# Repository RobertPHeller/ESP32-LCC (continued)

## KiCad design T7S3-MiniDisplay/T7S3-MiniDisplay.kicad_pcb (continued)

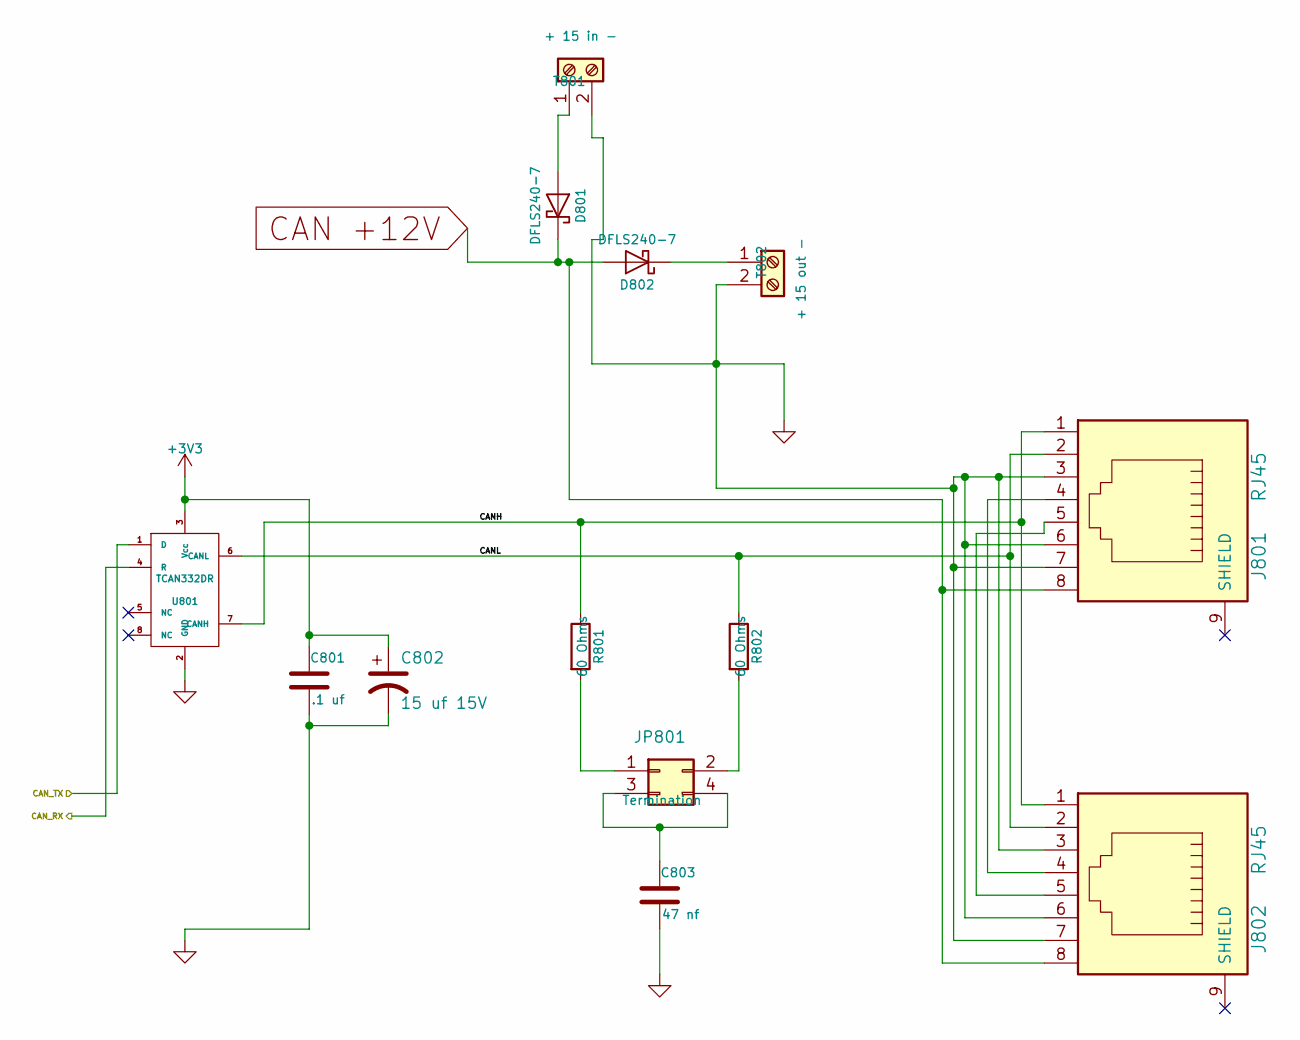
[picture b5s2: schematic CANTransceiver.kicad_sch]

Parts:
C801: .1 uf; C_0603_1608Metric; Mouser Part Number 80-C0603C104K5R7411
C802: 15 uf 15V; CP_Elec_4x5.7; Mouser Part Number 710-865080340002
C803: 47 nf; C_0603_1608Metric; Mouser Part Number 710-885012206093
D801, D802: DFLS240-7; D_PowerDI-123; Mouser Part Number 621-DFLS240-7
J801, J802: RJ45; RJ45_8N-S; Mouser Part Number 710-615008144221
JP801: Termination; PinHeader_2x02_P2.54mm_Vertical; Mouser Part Number 649-67997-404HLF
R801, R802: 60 Ohms; R_1206_3216Metric; Mouser Part Number 71-CRCW120660R0KNAIF
T801: + 15 in -; TerminalBlock_TE_282834-2_1x02_P2.54mm_Horizontal; Mouser Part Number 651-1725656
T802: + 15 out -; TerminalBlock_TE_282834-2_1x02_P2.54mm_Horizontal; Mouser Part Number 651-1725656
U801: TCAN332DR; SOIC-8_3.9x4.9mm_P1.27mm; Mouser Part Number 595-TCAN332DR

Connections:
+3V3: C801.1, C802.1, U801.3 (Vcc); also elsewhere on the board
/CAN Rx: U801.4 (R); also elsewhere on the board
/CAN Transceiver/CANH: J801.1, J802.1, R801.1, U801.7 (CANH)
/CAN Transceiver/CANL: J801.2, J802.2, R802.1, U801.6 (CANL)
/CAN Tx: U801.1 (D); also elsewhere on the board
CAN +12V: D801.1 (K), D802.2 (A), J801.8, J802.8; also elsewhere on the board
GND: C801.2, C802.2, C803.2, J801.3, J801.6, J801.7, J802.3, J802.6, J802.7, T801.2, T802.2, U801.2 (GND); also elsewhere on the board
unnamed: C803.1, JP801.3, JP801.4
unnamed: D801.2 (A), T801.1
unnamed: D802.1 (K), T802.1
unnamed: J801.4, J802.4
unnamed: J801.5, J802.5
unnamed: JP801.1, R801.2
unnamed: JP801.2, R802.2

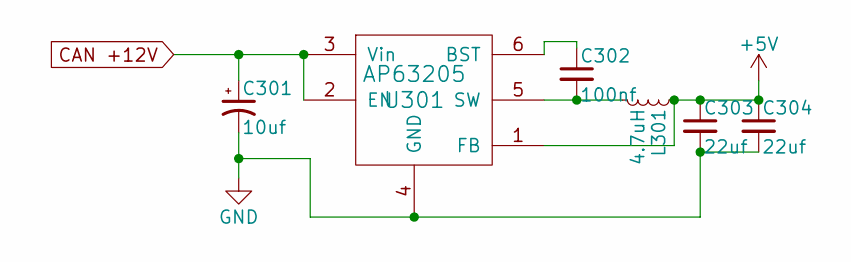
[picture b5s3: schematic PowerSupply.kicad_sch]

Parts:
C301: 10uf; CP_Elec_5x5.3; Mouser Part Number 667-EEE-HB1C100R
C302: 100nf; C_0603_1608Metric; Mouser Part Number 710-885012206020
C303, C304: 22uf; C_0603_1608Metric; Mouser Part Number 603-CC0603MRX6S5B226
L301: 4.7uH; L_7.3x7.3_H4.5; Mouser Part Number 81-B1047AS-4R7N=P3
U301: AP63205; TSOT-23-6; Mouser Part Number 621-AP63205WU-7

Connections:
+5V: C303.1, C304.1, L301.1, U301.1 (FB); also elsewhere on the board
CAN +12V: C301.1, U301.2 (EN), U301.3 (Vin); also elsewhere on the board
GND: C301.2, C303.2, C304.2, U301.4 (GND); also elsewhere on the board
unnamed: C302.1, U301.6 (BST)
unnamed: C302.2, L301.2, U301.5 (SW)

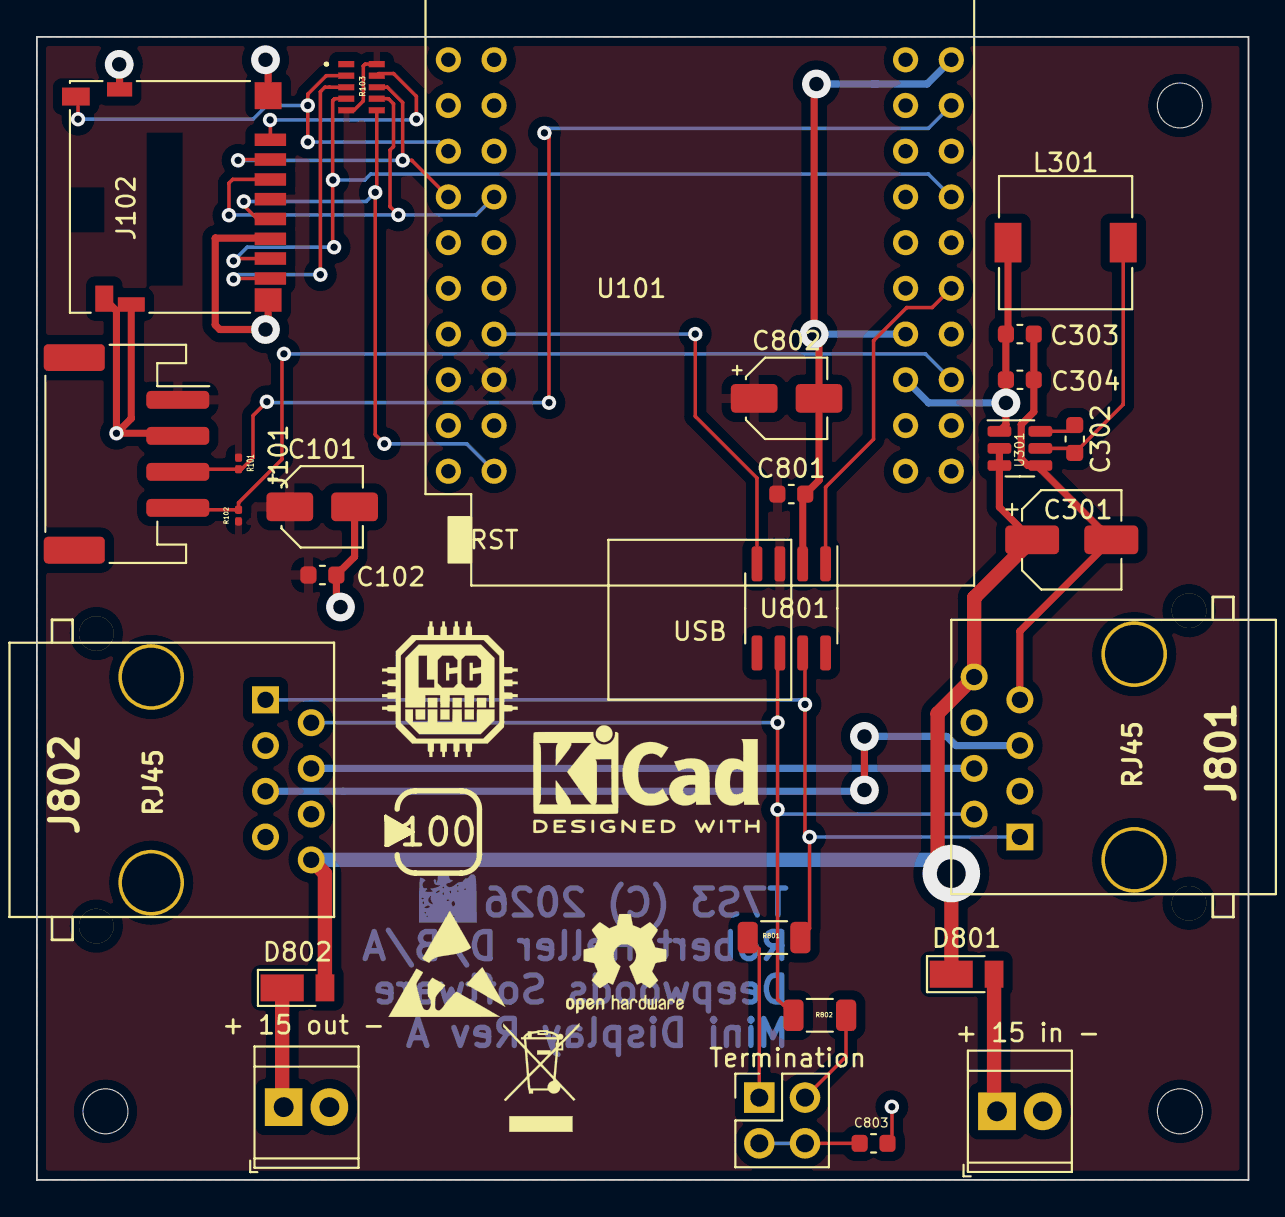
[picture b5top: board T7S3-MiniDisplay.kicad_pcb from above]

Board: 2 copper layers, 67.3 x 63.5 mm, 30 parts (0 on the bottom side), 26 nets.

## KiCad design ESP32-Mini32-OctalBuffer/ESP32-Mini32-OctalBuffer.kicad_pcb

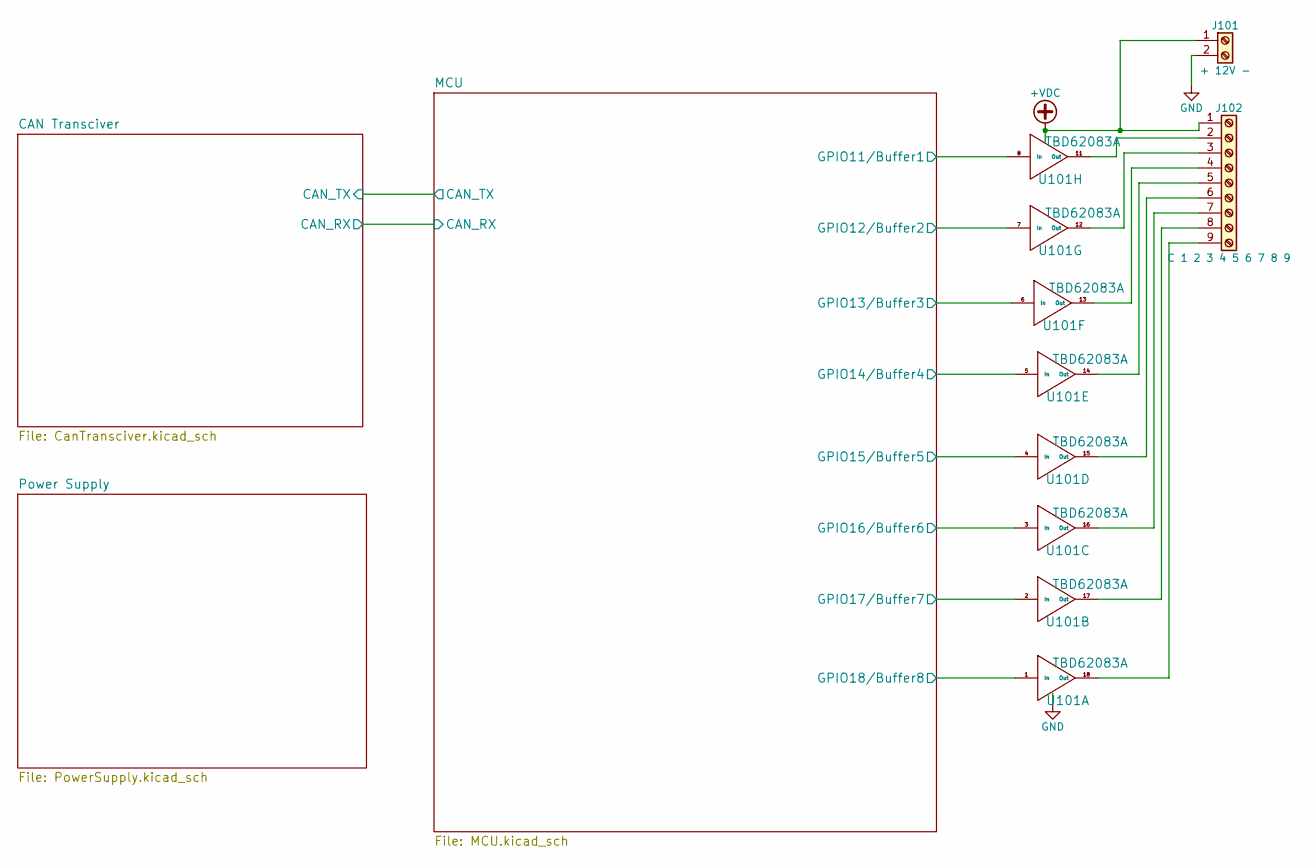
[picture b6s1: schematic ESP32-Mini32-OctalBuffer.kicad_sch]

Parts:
J101: + 12V -; TerminalBlock_Pheonix_PT-3.5mm_2pol
J102: C 1 2 3 4 5 6 7 8 9; TerminalBlock_Pheonix_PT-3.5mm_9pol
U101: TBD62083A; SOIC-18W_7.5x11.6mm_Pitch1.27mm; Mouser Part Number 757-TBD62083AFGEL

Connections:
+VDC: J101.1, J102.1, U101.10 (OC)
/MCU/GPIO11/Buffer1: U101.8 (In); also elsewhere on the board
/MCU/GPIO12/Buffer2: U101.7 (In); also elsewhere on the board
/MCU/GPIO13/Buffer3: U101.6 (In); also elsewhere on the board
/MCU/GPIO14/Buffer4: U101.5 (In); also elsewhere on the board
/MCU/GPIO15/Buffer5: U101.4 (In); also elsewhere on the board
/MCU/GPIO16/Buffer6: U101.3 (In); also elsewhere on the board
/MCU/GPIO17/Buffer7: U101.2 (In); also elsewhere on the board
/MCU/GPIO18/Buffer8: U101.1 (In); also elsewhere on the board
GND: J101.2, U101.9 (IC); also elsewhere on the board
unnamed: J102.2, U101.11 (Out)
unnamed: J102.3, U101.12 (Out)
unnamed: J102.4, U101.13 (Out)
unnamed: J102.5, U101.14 (Out)
unnamed: J102.6, U101.15 (Out)
unnamed: J102.7, U101.16 (Out)
unnamed: J102.8, U101.17 (Out)
unnamed: J102.9, U101.18 (Out)

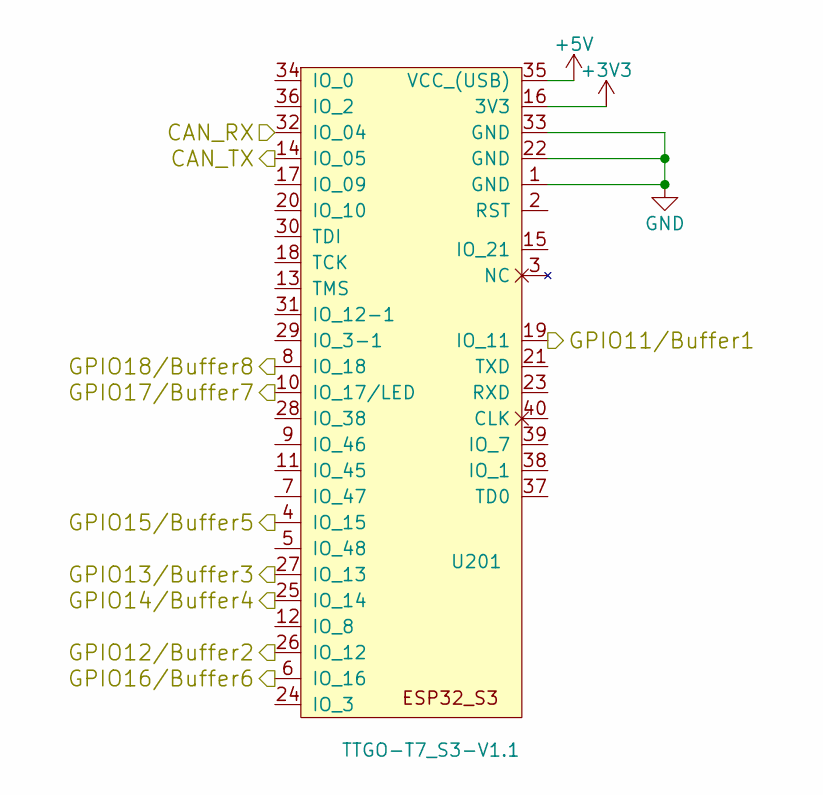
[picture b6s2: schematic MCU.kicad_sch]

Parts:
U201: TTGO-T7_S3-V1.1; ESP32_mini

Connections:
+3V3: U201.16 (3V3); also elsewhere on the board
+5V: U201.35 (VCC_(USB)); also elsewhere on the board
/CAN Transciver/CAN_RX: U201.32 (IO_04); also elsewhere on the board
/CAN Transciver/CAN_TX: U201.14 (IO_05); also elsewhere on the board
/MCU/GPIO11/Buffer1: U201.19 (IO_11); also elsewhere on the board
/MCU/GPIO12/Buffer2: U201.26 (IO_12); also elsewhere on the board
/MCU/GPIO13/Buffer3: U201.27 (IO_13); also elsewhere on the board
/MCU/GPIO14/Buffer4: U201.25 (IO_14); also elsewhere on the board
/MCU/GPIO15/Buffer5: U201.4 (IO_15); also elsewhere on the board
/MCU/GPIO16/Buffer6: U201.6 (IO_16); also elsewhere on the board
/MCU/GPIO17/Buffer7: U201.10 (IO_17/LED); also elsewhere on the board
/MCU/GPIO18/Buffer8: U201.8 (IO_18); also elsewhere on the board
GND: U201.1 (GND), U201.22 (GND), U201.33 (GND); also elsewhere on the board

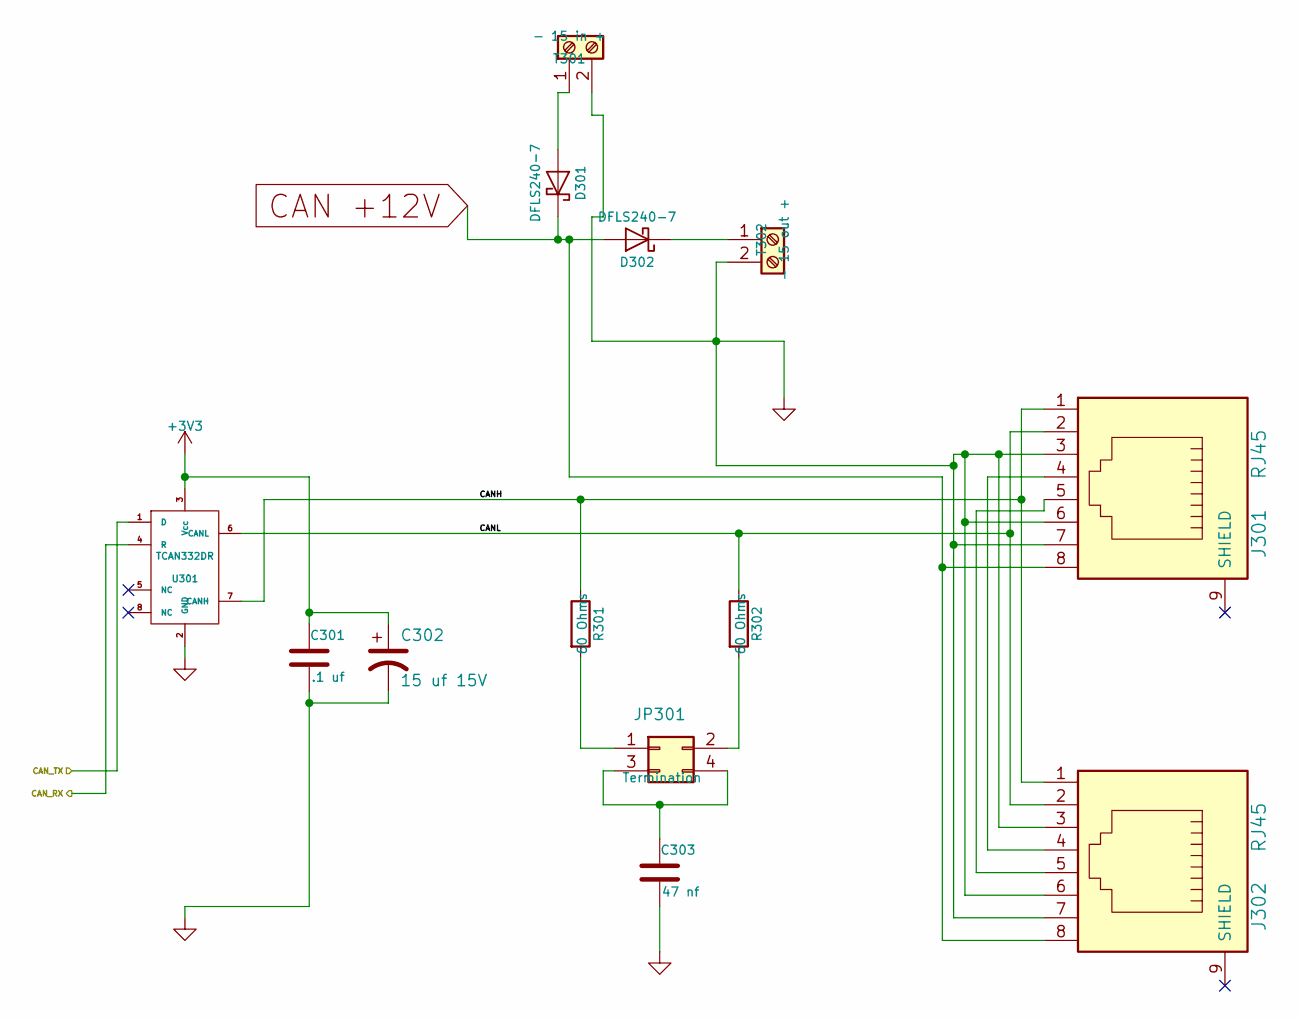
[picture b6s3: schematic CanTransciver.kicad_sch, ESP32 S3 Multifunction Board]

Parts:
C301: .1 uf; C_0603; Mouser Part Number 710-885012206095
C302: 15 uf 15V; CP_Elec_4x5.7; Mouser Part Number 647-UUD1C150MCL
C303: 47 nf; C_0603; Mouser Part Number 710-885012206093
D301, D302: DFLS240-7; D_PowerDI-123; Mouser Part Number 621-DFLS240-7
J301, J302: RJ45; RJ45_8N-S; Mouser Part Number 710-615008144221
JP301: Termination; Pin_Header_Straight_2x02_Pitch2.54mm; Mouser Part Number 649-67997-404HLF
R301, R302: 60 Ohms; R_0603_1608Metric_Pad0.98x0.95mm_HandSolder; Mouser Part Number 72-P0603C60R0BNTA
T301: - 15 in +; TerminalBlock_Pheonix_MPT-2.54mm_2pol; Mouser Part Number 651-1725656
T302: - 15 out +; TerminalBlock_Pheonix_MPT-2.54mm_2pol; Mouser Part Number 651-1725656
U301: TCAN332DR; SOIC-8_3.9x4.9mm_Pitch1.27mm; Mouser Part Number 595-TCAN332DR

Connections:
+3V3: C301.1, C302.1, U301.3 (Vcc); also elsewhere on the board
/CAN Transciver/CANH: J301.1, J302.1, R301.1, U301.7 (CANH)
/CAN Transciver/CANL: J301.2, J302.2, R302.1, U301.6 (CANL)
/CAN Transciver/CAN_RX: U301.4 (R); also elsewhere on the board
/CAN Transciver/CAN_TX: U301.1 (D); also elsewhere on the board
CAN +12V: D301.1 (K), D302.2 (A), J301.8, J302.8; also elsewhere on the board
GND: C301.2, C302.2, C303.2, J301.3, J301.6, J301.7, J302.3, J302.6, J302.7, T301.2, T302.2, U301.2 (GND); also elsewhere on the board
unnamed: C303.1, JP301.3, JP301.4
unnamed: D301.2 (A), T301.1
unnamed: D302.1 (K), T302.1
unnamed: J301.4, J302.4
unnamed: J301.5, J302.5
unnamed: JP301.1, R301.2
unnamed: JP301.2, R302.2

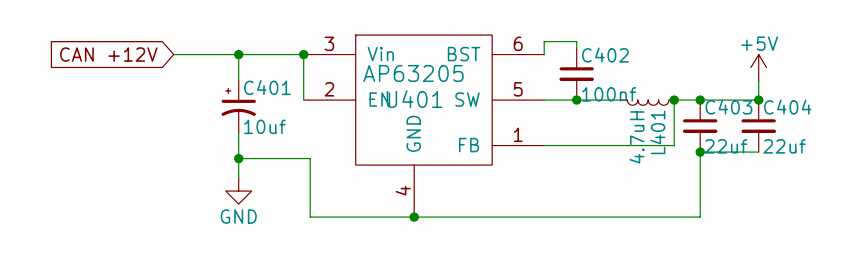
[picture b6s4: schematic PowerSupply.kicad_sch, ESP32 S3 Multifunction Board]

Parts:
C401: 10uf; CP_Elec_5x5.3; Mouser Part Number 710-865230542002
C402: 100nf; C_0603; Mouser Part Number 710-885012206020
C403, C404: 22uf; C_0603; Mouser Part Number 603-CC0603MRX6S5B226
L401: 4.7uH; L_7.3x7.3_H4.5; Mouser Part Number 81-B1047AS-4R7NP3
U401: AP63205; TSOT-23-6_MK06A; Mouser Part Number 621-AP63205WU-7

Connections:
+5V: C403.1, C404.1, L401.1, U401.1 (FB); also elsewhere on the board
CAN +12V: C401.1, U401.2 (EN), U401.3 (Vin); also elsewhere on the board
GND: C401.2, C403.2, C404.2, U401.4 (GND); also elsewhere on the board
unnamed: C402.1, U401.6 (BST)
unnamed: C402.2, L401.2, U401.5 (SW)

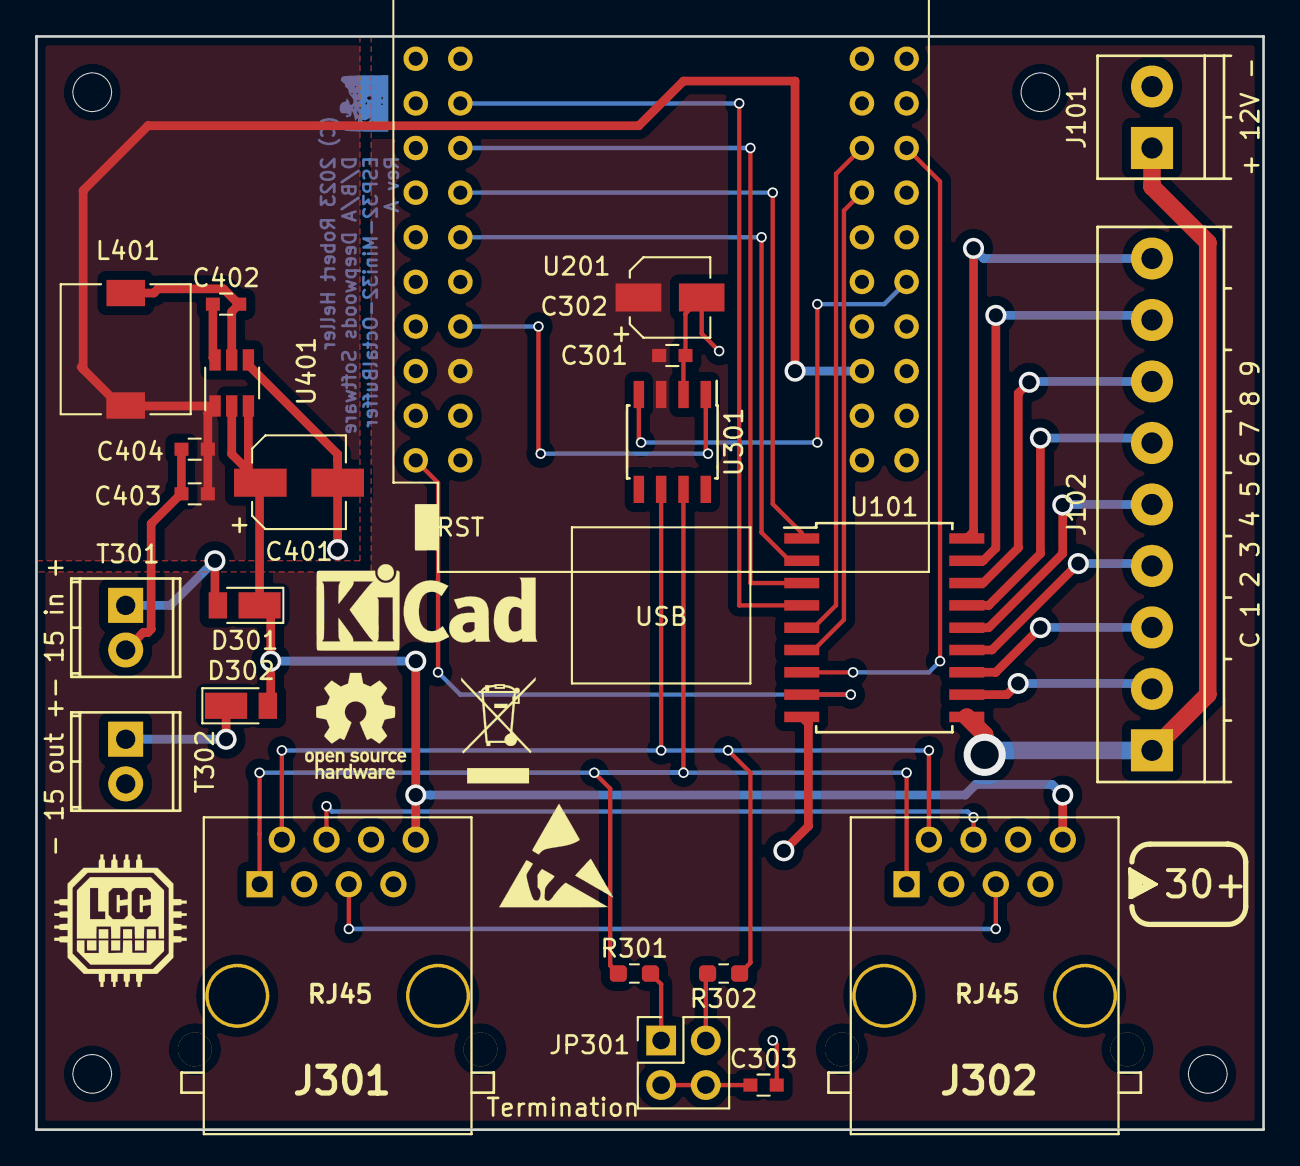
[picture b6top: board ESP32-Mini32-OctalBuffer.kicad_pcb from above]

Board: 2 copper layers, 69.9 x 62.2 mm, 23 parts (0 on the bottom side), 34 nets.

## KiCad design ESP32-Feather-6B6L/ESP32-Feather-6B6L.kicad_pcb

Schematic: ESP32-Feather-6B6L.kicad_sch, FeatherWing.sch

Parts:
MS1: FEATHERWING

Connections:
+3V3: MS1.2 (3V); also elsewhere on the board
+5V: MS1.26 (USB); also elsewhere on the board
/AREF: MS1.3 (AREF)
/CAN_RX: MS1.9 (GPIOA4); also elsewhere on the board
/CAN_TX: MS1.10 (GPIOA5); also elsewhere on the board
/N$1: MS1.27 (EN)
/N$2: MS1.16 (NC)
/N$3: MS1.25 (GPIO13); also elsewhere on the board
/N$4: MS1.15 (GPIOTX)
/N$5: MS1.24 (GPIO12); also elsewhere on the board
/N$6: MS1.14 (GPIORX)
/N$7: MS1.13 (GPIOMISO); also elsewhere on the board
/N$8: MS1.12 (GPIOMOSI); also elsewhere on the board
/N$9: MS1.11 (GPIOSCK); also elsewhere on the board
/N$12: MS1.8 (GPIOA3); also elsewhere on the board
/N$13: MS1.7 (GPIOA2); also elsewhere on the board
/N$14: MS1.6 (GPIOA1); also elsewhere on the board
/N$15: MS1.5 (GPIOA0); also elsewhere on the board
/N$18: MS1.1 (~RESET)
/N$19: MS1.23 (GPIO11); also elsewhere on the board
/N$20: MS1.22 (GPIO10); also elsewhere on the board
/N$21: MS1.21 (GPIO9); also elsewhere on the board
/N$22: MS1.20 (GPIO6); also elsewhere on the board
/N$23: MS1.19 (GPIO5); also elsewhere on the board
/N$24: MS1.18 (GPIOSCL)
/N$25: MS1.17 (GPIOSDA)
/VBAT: MS1.28 (VBAT)
GND: MS1.4 (GND); also elsewhere on the board

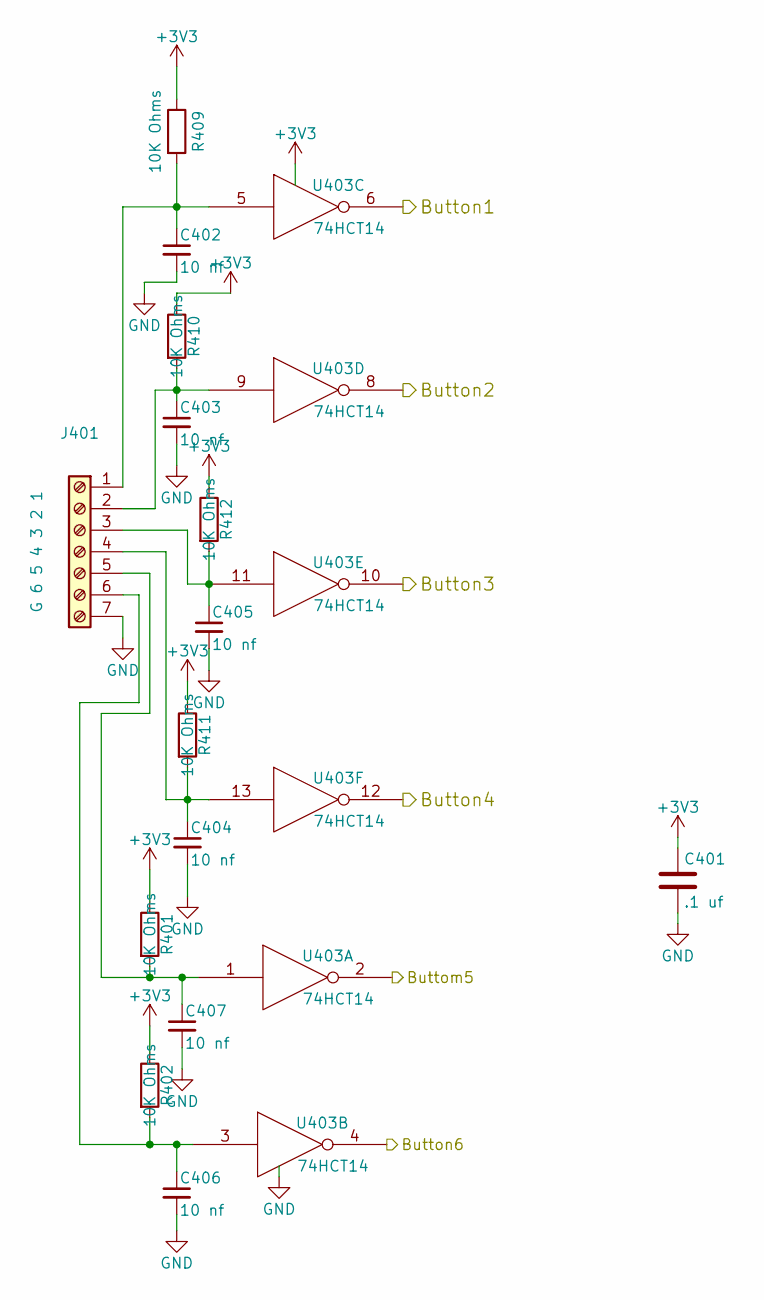
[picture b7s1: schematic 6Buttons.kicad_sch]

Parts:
C401: .1 uf; C_Rect_L4.0mm_W2.5mm_P2.50mm; Mouser Part Number 810-FA18X8R1E104KNU6
C402, C403, C404, C405, C406, C407: 10 nf; C_Rect_L4.0mm_W2.5mm_P2.50mm; Mouser Part Number 80-C320C103K3G5TA
J401: G 6 5 4 3 2 1; TerminalBlock_TE_282834-7_1x07_P2.54mm_Horizontal; Mouser Part Number 571-282834-7
R401, R402, R409, R410, R411, R412: 10K Ohms; R_Axial_DIN0204_L3.6mm_D1.6mm_P2.54mm_Vertical; Mouser Part Number 708-CF18JT10K0
U403: 74HCT14; DIP-14_W7.62mm; Mouser Part Number 595-CD74HC14E

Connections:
+3V3: C401.1, R401.1, R402.1, R409.1, R410.1, R411.1, R412.1, U403.14 (VCC); also elsewhere on the board
/N$8: U403.4; also elsewhere on the board
/N$9: U403.2; also elsewhere on the board
/N$12: U403.12; also elsewhere on the board
/N$13: U403.10; also elsewhere on the board
/N$14: U403.8; also elsewhere on the board
/N$15: U403.6; also elsewhere on the board
GND: C401.2, C402.2, C403.2, C404.2, C405.2, C406.2, C407.2, J401.7, U403.7 (GND); also elsewhere on the board
unnamed: C402.1, J401.1, R409.2, U403.5
unnamed: C403.1, J401.2, R410.2, U403.9
unnamed: C404.1, J401.4, R411.2, U403.13
unnamed: C405.1, J401.3, R412.2, U403.11
unnamed: C406.1, J401.6, R402.2, U403.3
unnamed: C407.1, J401.5, R401.2, U403.1

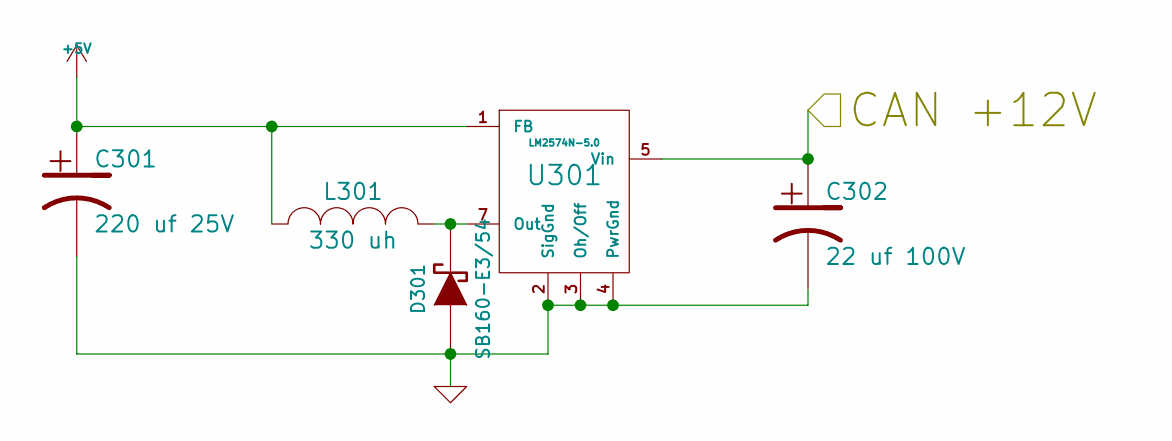
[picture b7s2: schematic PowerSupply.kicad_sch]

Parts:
C301: 220 uf 25V; CP_Radial_D8.0mm_P3.50mm; Mouser Part Number 140-REA221M1EBK0811P
C302: 22 uf 100V; CP_Radial_D8.0mm_P3.50mm; Mouser Part Number 140-REA220M2ABK0811P
D301: SB160-E3/54; D_DO-41_SOD81_P7.62mm_Horizontal; Mouser Part Number 625-SB160-E3
L301: 330 uh; PE-LowProfile; Mouser Part Number 673-PE-52627NL
U301: LM2574N-5.0; DIP-8_W7.62mm; Mouser Part Number 926-LM2574N-5.0/NOPB

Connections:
+5V: C301.1, L301.1, U301.1 (FB); also elsewhere on the board
/CAN Transceiver/+12V CAN Power: C302.1, U301.5 (Vin); also elsewhere on the board
GND: C301.2, C302.2, D301.1 (A), U301.2 (SigGnd), U301.3 (Oh/Off), U301.4 (PwrGnd); also elsewhere on the board
unnamed: D301.2 (K), L301.2, U301.7 (Out)

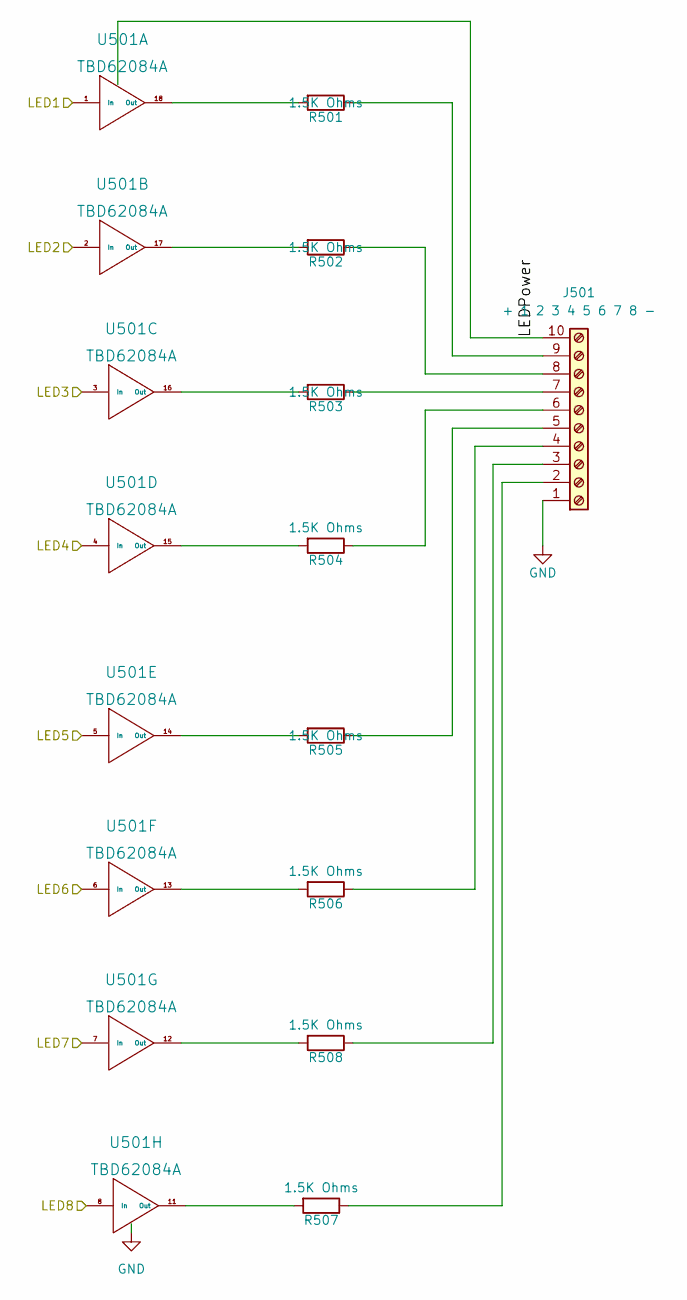
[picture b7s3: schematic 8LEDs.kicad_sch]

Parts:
J501: + 1 2 3 4 5 6 7 8 -; TerminalBlock_Phoenix_MPT-0,5-10-2.54_1x10_P2.54mm_Horizont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
R501, R502, R503, R504, R505, R506, R507, R508: 1.5K Ohms; R_Axial_DIN0204_L3.6mm_D1.6mm_P7.62mm_Horizontal; Mouser Part Number 603-CFR-25JR-52-1K5
U501: TBD62084A; DIP-18_W7.62mm

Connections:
/Eight LEDs/LEDPower: J501.10, U501.10 (OC)
/N$3: U501.1 (In); also elsewhere on the board
/N$5: U501.2 (In); also elsewhere on the board
/N$7: U501.8 (In); also elsewhere on the board
/N$19: U501.3 (In); also elsewhere on the board
/N$20: U501.4 (In); also elsewhere on the board
/N$21: U501.5 (In); also elsewhere on the board
/N$22: U501.6 (In); also elsewhere on the board
/N$23: U501.7 (In); also elsewhere on the board
GND: J501.1, U501.9 (IC); also elsewhere on the board
unnamed: J501.2, R507.1
unnamed: J501.3, R508.1
unnamed: J501.4, R506.1
unnamed: J501.5, R505.1
unnamed: J501.6, R504.1
unnamed: J501.7, R503.1
unnamed: J501.8, R502.1
unnamed: J501.9, R501.1
unnamed: R501.2, U501.18 (Out)
unnamed: R502.2, U501.17 (Out)
unnamed: R503.2, U501.16 (Out)
unnamed: R504.2, U501.15 (Out)
unnamed: R505.2, U501.14 (Out)
unnamed: R506.2, U501.13 (Out)
unnamed: R507.2, U501.11 (Out)
unnamed: R508.2, U501.12 (Out)

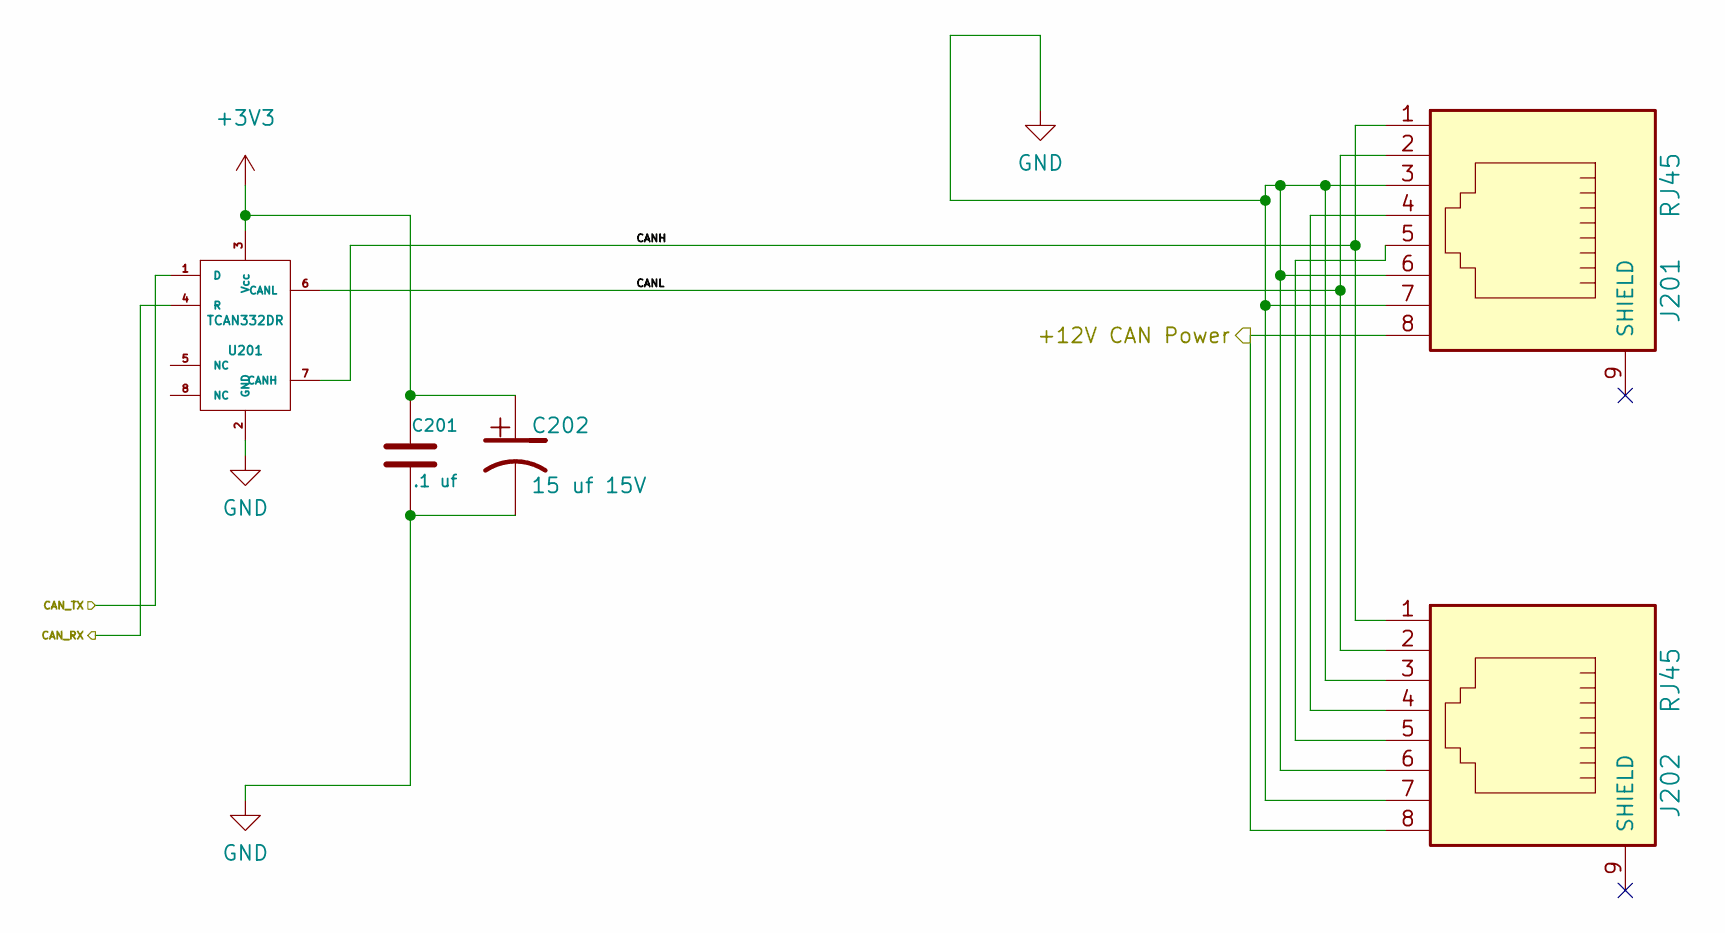
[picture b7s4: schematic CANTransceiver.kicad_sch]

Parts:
C201: .1 uf; C_Rect_L4.0mm_W2.5mm_P2.50mm; Mouser Part Number 21RZ310-RC
C202: 15 uf 15V; CP_Radial_D6.3mm_P2.50mm; Mouser Part Number 710-860080773002
J201, J202: RJ45; RJ45_8N-S; Mouser Part Number 710-615008144221
U201: TCAN332DR; SOIC-8_3.9x4.9mm_P1.27mm; Mouser Part Number 595-TCAN332DR

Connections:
+3V3: C201.1, C202.1, U201.3 (Vcc); also elsewhere on the board
/CAN Transceiver/+12V CAN Power: J201.8, J202.8; also elsewhere on the board
/CAN Transceiver/CANH: J201.1, J202.1, U201.7 (CANH)
/CAN Transceiver/CANL: J201.2, J202.2, U201.6 (CANL)
/CAN_RX: U201.4 (R); also elsewhere on the board
/CAN_TX: U201.1 (D); also elsewhere on the board
GND: C201.2, C202.2, J201.3, J201.6, J201.7, J202.3, J202.6, J202.7, U201.2 (GND); also elsewhere on the board
unnamed: J201.4, J202.4
unnamed: J201.5, J202.5

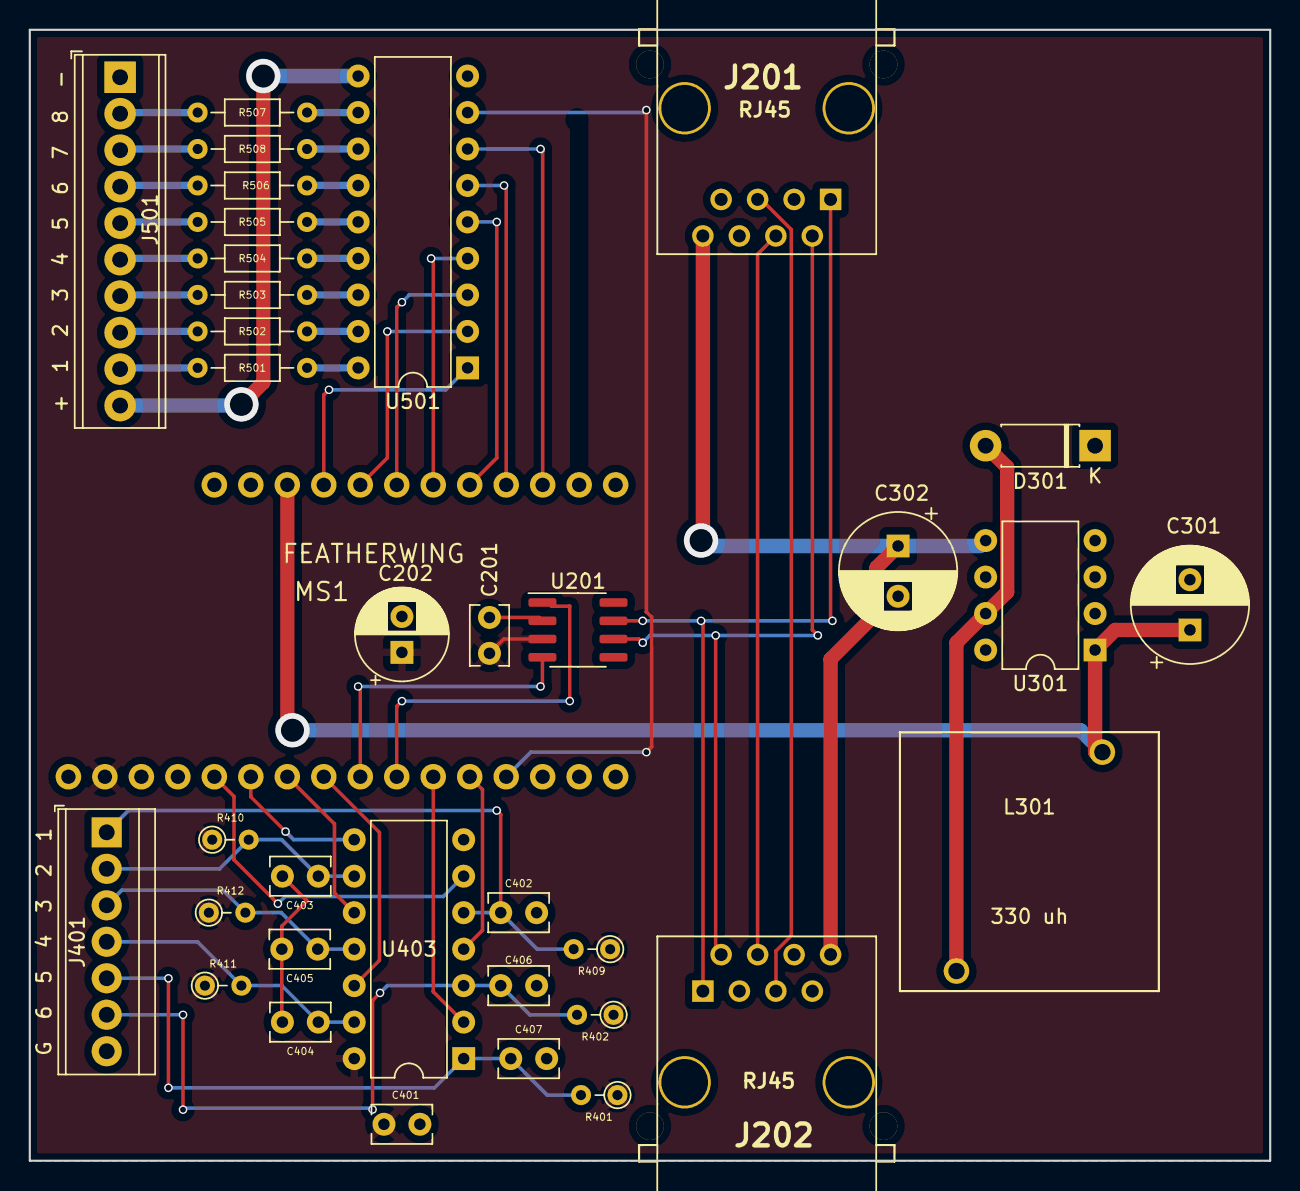
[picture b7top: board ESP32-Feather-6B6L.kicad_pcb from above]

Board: 2 copper layers, 86.4 x 78.7 mm, 36 parts (0 on the bottom side), 48 nets.
